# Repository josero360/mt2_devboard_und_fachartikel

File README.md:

# Konsant Stromsenke
Ist als Fachartikel an der OTH Regensburg im Fach Messtechnik 2 gestartet.
Development Board ist aus Interesse gestartet worden. 
Durch den OP LTC2057, mit seiner Shutdown Funktion (oder jeden anderen der die Funktion besitzt), könnten mehrere Boards parallel geschaltet werden und so unterschiedliche Strombereiche nutzbar gemacht werden.
Software auf einem TI Tiva LauchPad ist geplant.
Diese soll neben dem messen (U/I) und berechnen (P) noch Überstrom-/Temperaturschutz realisieren.

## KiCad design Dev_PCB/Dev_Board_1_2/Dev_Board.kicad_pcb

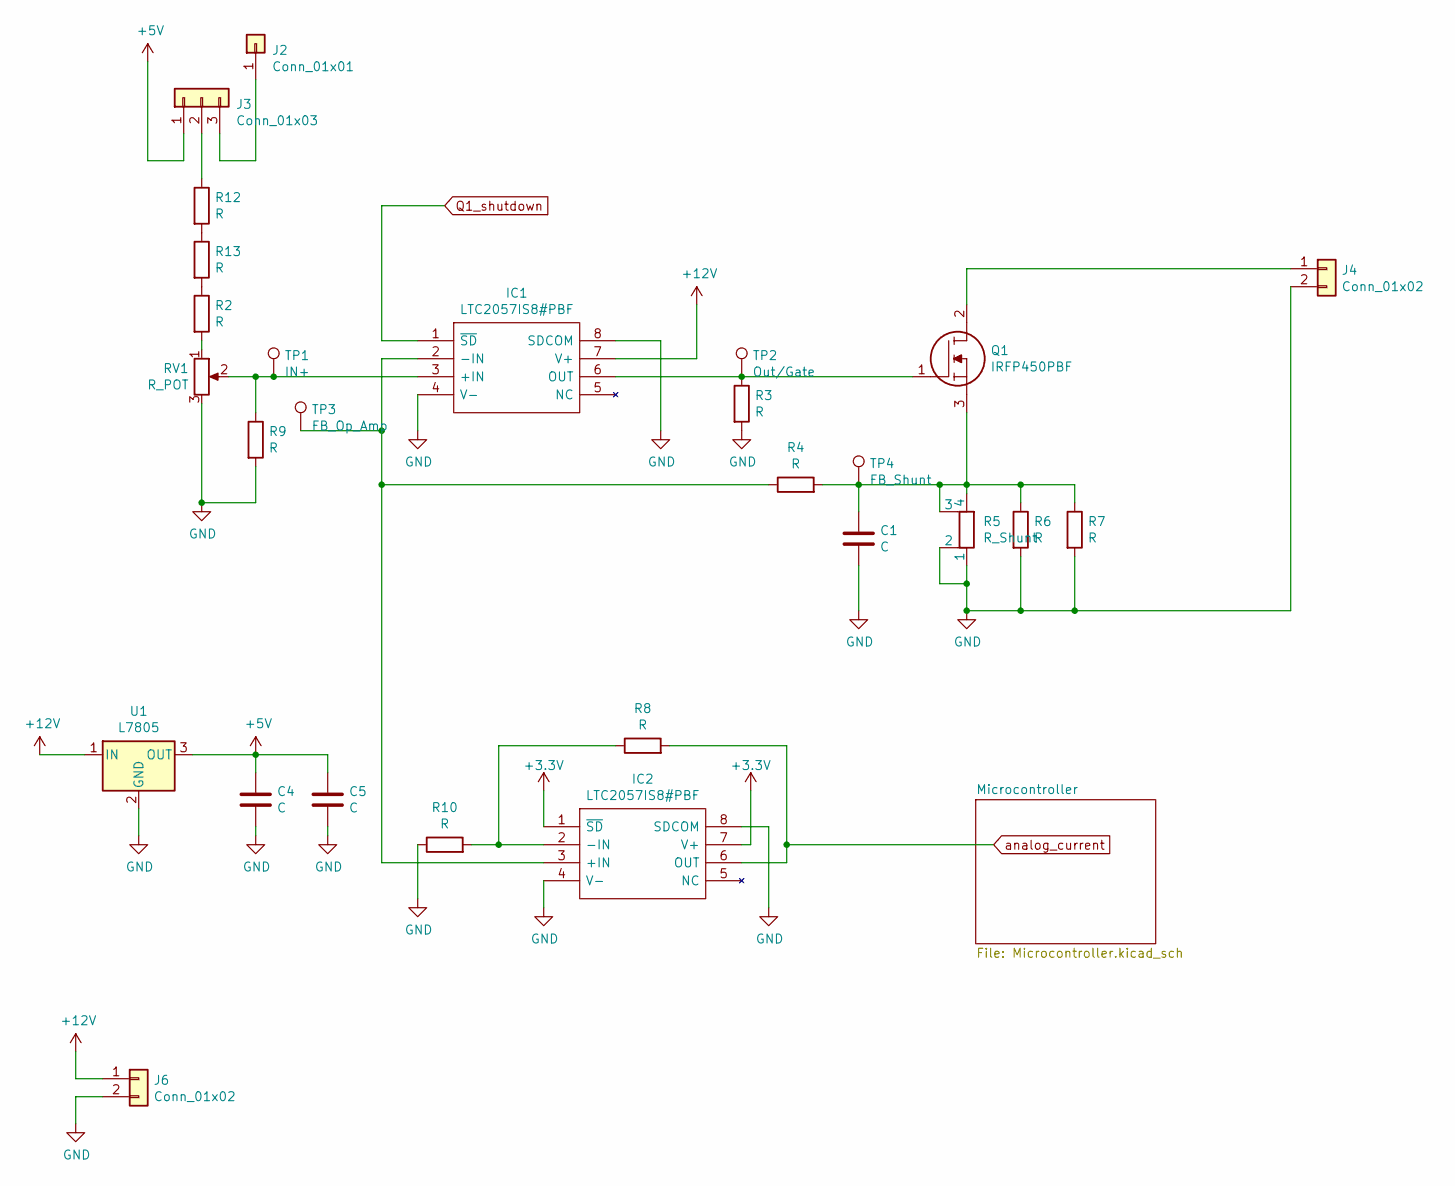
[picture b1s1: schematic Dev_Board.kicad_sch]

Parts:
C1, C4, C5: C; C_1206_3216Metric_Pad1.33x1.80mm_HandSolder
IC1, IC2: LTC2057IS8#PBF; SOIC127P599X175-8N; Manufacturer_Part_Number LTC2057IS8#PBF; Mouser Part Number 584-LTC2057IS8#PBF
J2: Conn_01x01; Banana_Jack_1Pin
J3: Conn_01x03; PinHeader_1x03_P2.54mm_Vertical
J4, J6: Conn_01x02; Banana_Jack_2Pin
Q1: IRFP450PBF; TO544P521X1568X2486-3P; Manufacturer_Part_Number IRFP450PBF; Mouser Part Number 844-IRFP450PBF
R2, R3, R4, R7, R8, R9, R10, R12, R13: R; R_0207_Axial_1206_SMD_Mix
R5: R_Shunt; PBV_Shunt
R6: R; R_2816_7142Metric_Pad3.20x4.45mm_HandSolder
RV1: R_POT; Potentiometer_Alpha_RD901F-40-00D_Single_Vertical_CircularH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
TP1: IN+; TestPoint_2Pads_Pitch2.54mm_Drill0.8mm
TP2: Out/Gate; TestPoint_2Pads_Pitch2.54mm_Drill0.8mm
TP3: FB_Op_Amp; TestPoint_2Pads_Pitch2.54mm_Drill0.8mm
TP4: FB_Shunt; TestPoint_2Pads_Pitch2.54mm_Drill0.8mm
U1: L7805; TO-220-3_Horizontal_TabDown

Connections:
+5V: C4.1, C5.1, J3.1, U1.3 (OUT)
+12V: IC1.7 (V+), IC2.1 (~SD), IC2.7 (V+), J6.1, U1.1 (IN); also elsewhere on the board
GND: C1.2, C4.2, C5.2, IC1.4 (V-), IC1.8 (SDCOM), IC2.4 (V-), IC2.8 (SDCOM), J4.2, J6.2, R3.2, R5.1, R5.2, R6.2, R7.2, R9.2, R10.1, RV1.3, U1.2 (GND); also elsewhere on the board
unnamed: C1.1, Q1.3, R4.2, R5.3, R5.4, R6.1, R7.1, TP4.1
unnamed 4: IC1.1 (~SD); also elsewhere on the board
unnamed: IC1.2 (-IN), IC2.3 (+IN), R4.1, TP3.1
unnamed: IC1.3 (+IN), R9.1, RV1.2, TP1.1
unnamed: IC1.6 (OUT), Q1.1, R3.1, TP2.1
unnamed: IC2.2 (-IN), R8.1, R10.2
unnamed 11: IC2.6 (OUT), R8.2; also elsewhere on the board
unnamed: J2.1, J3.3
unnamed: J3.2, R12.1
unnamed: J4.1, Q1.2
unnamed: R2.2, RV1.1
unnamed: R12.2, R13.1
unnamed: R2.1, R13.2

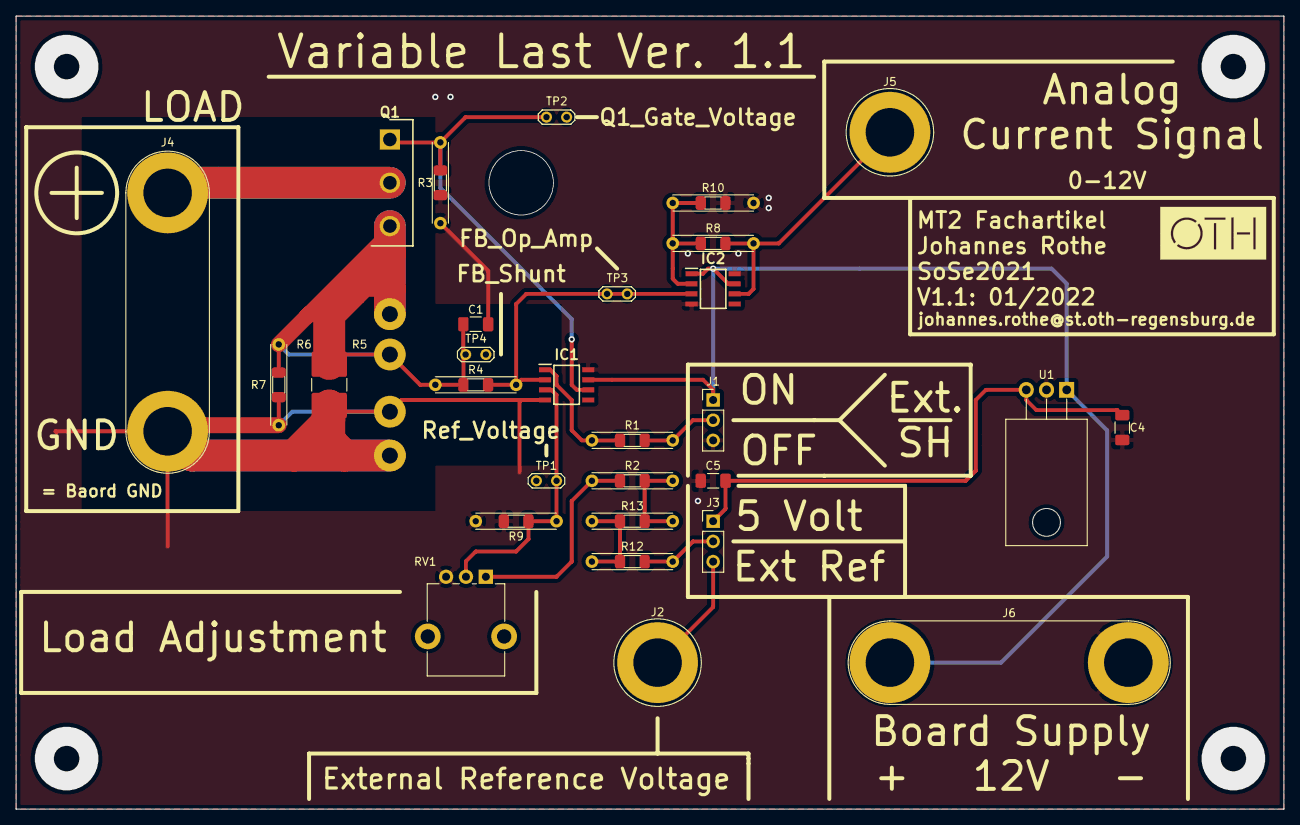
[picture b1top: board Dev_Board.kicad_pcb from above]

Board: 2 copper layers, 159.4 x 99.7 mm, 30 parts (0 on the bottom side), 17 nets.

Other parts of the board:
J1: Conn_01x03; PinHeader_1x03_P2.54mm_Vertical
J5: Conn_01x01; Banana_Jack_1Pin
R1: R; R_0207_Axial_1206_SMD_Mix

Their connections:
+12V: J1.1; also elsewhere on the board
GND: J1.3; also elsewhere on the board
unnamed 4: R1.2; also elsewhere on the board
unnamed 11: J5.1; also elsewhere on the board
unnamed: J1.2, R1.1

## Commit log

2022-02-05 Intial Commit
2022-02-05 Created Readme
2022-02-05 added software plans and datasheets
2022-03-05 created dev board 1.2
2022-03-05 created dev board 1.2 (really)
2022-03-05 not working test software for display (ST7735)
2022-03-05 changed test main.c to main.cpp
